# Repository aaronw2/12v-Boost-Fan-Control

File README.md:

# 12v-Boost-Fan-Control
This is a small board designed to boost 3-8v (typically 5v) up to 12v. 
In addition, it contains a N-channel mosfet which can be used to turn
a device on or off or to perform PWM on something like a fan.

This board was designed to efficiently power 12v computer fans using as
small a footprint as possible.  While it's certainly possible to go
smaller, this uses 0603 and larger devices.

On the input side there is +5, ground and a FET control line.  To
enable the FET as a ground type device, pull the FET control line
to 3v or higher and connect the device between +12 and FET-.  Note
that when the fet is not activated that the FET- will not provide 
ground.

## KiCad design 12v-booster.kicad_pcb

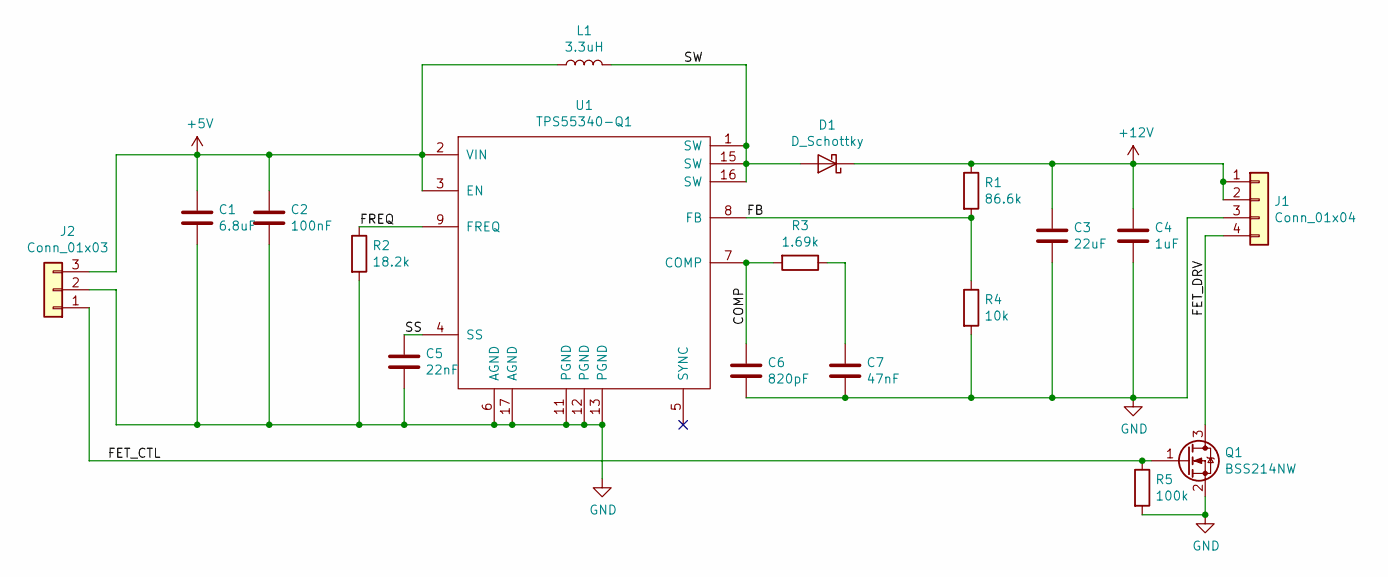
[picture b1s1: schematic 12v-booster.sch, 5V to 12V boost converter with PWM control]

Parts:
C1: 6.8uF; C_0603_1608Metric; MPN C1608X5R1E685K080AC
C2: 100nF; C_0603_1608Metric; MPN CL10B104KO8WPNC
C3: 22uF; C_1210_3225Metric; MPN CL32B226MOJNNNE
C4: 1uF; C_0603_1608Metric; MPN CL10B105KP8NNNC
C5: 22nF; C_0603_1608Metric; MPN CL10B223KB8WPNC
C6: 820pF; C_0603_1608Metric; MPN C0603C821J5RACTU
C7: 47nF; C_0603_1608Metric; MPN GRM188R61H474KA12D
D1: D_Schottky; D_SOD-123F; MPN SS24FL
J1: Conn_01x04; PinHeader_1x04_P2.54mm_Horizontal
J2: Conn_01x03; PinHeader_1x03_P2.54mm_Horizontal
L1: 3.3uH; L_Vishay_IHLP-1212; MPN IHLP1212BZER3R3M11
Q1: BSS214NW; SOT-323_SC-70; MPN BSS214NWH6327XTSA1
R1: 86.6k; R_0603_1608Metric; MPN CRCW060386K6FKEA
R2: 18.2k; R_0603_1608Metric; MPN CRCW060318K2FKEA
R3: 1.69k; R_0603_1608Metric; MPN CRCW06031K69FKEA
R4: 10k; R_0603_1608Metric; MPN CRCW060310K0FKEC
R5: 100k; R_0603_1608Metric; MPN CRG0603F100K
U1: TPS55340-Q1; QFN-16-1EP_3x3mm_P0.5mm_EP2.7x2.7mm_ThermalVias; MPN TPS55340RTER

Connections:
+5V: C1.1, C2.1, J2.3, L1.1, U1.2 (VIN), U1.3 (EN)
+12V: C3.1, C4.1, D1.1 (K), J1.1, J1.2, R1.1
/COMP: C6.1, R3.2, U1.7 (COMP)
/FB: R1.2, R4.1, U1.8 (FB)
/FET_CTL: J2.1, Q1.1 (G), R5.1
/FET_DRV: J1.4, Q1.3 (D)
/FREQ: R2.1, U1.9 (FREQ)
/SS: C5.1, U1.4 (SS)
/SW: D1.2 (A), L1.2, U1.1 (SW), U1.15 (SW), U1.16 (SW)
GND: C1.2, C2.2, C3.2, C4.2, C5.2, C6.2, C7.2, J1.3, J2.2, Q1.2 (S), R2.2, R4.2, R5.2, U1.6 (AGND), U1.11 (PGND), U1.12 (PGND), U1.13 (PGND), U1.17 (AGND)
unnamed: C7.1, R3.1

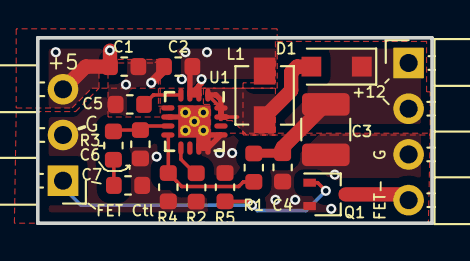
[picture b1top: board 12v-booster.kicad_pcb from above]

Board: 2 copper layers, 21.9 x 10.3 mm, 18 parts (0 on the bottom side), 11 nets.

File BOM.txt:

Designator	Value		Footprint	Part Number
C1		6.8uF		0603
C2		0.1uF		0603
C3		22uF 16V	1210
C4		1uF		0603
C5		0.022uF		0603
C6		820pf		0603
C7		0.047uF		0603
D1		Shottky 40V 2A	SOD-123F	ON Semi SS24FL
L1		3.3uH		IHLP-1212	Vishay IHLP1212BZER3R3M11
Q1		Mosfet N-CH	SOT-23		Infineon BSS214NW
R1		86.6K		0603
R2		18.2K		0603
R3		1.69K		0603
R4		10K 1%		0603
R5		100K		0603
U1		TI TPS55340	QFN-16-1EP 3x3mm 0.5mm pitch therm via

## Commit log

2018-09-26 Initial commit of revision 1.1.
2018-09-26 Added license.
2018-09-26 Updated page size and description in schematic.
2018-10-11 Fixed solder mask clearance.
2018-10-22 - Changed one ground to be +12V for 2 12V output pins - Cleaned up silkscreen
2018-10-22 Added BOM
2019-01-26 Fixed solder mask clearance
2019-11-15 Revision 1.2.2

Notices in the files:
12v-booster.kicad_pcb:
Copyright © 2018 by Aaron Williams
12v-booster.sch:
Copyright (C) 2018 by Aaron Williams
